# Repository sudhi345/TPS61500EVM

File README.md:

# TPS61500EVM
Evaluation board for TPS61500 high brightness led driver

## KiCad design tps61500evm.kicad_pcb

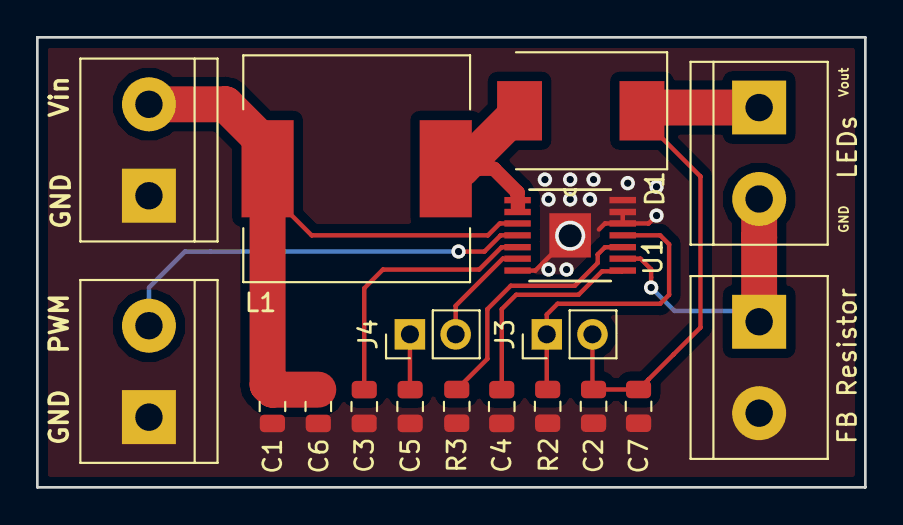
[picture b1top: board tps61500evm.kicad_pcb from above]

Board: 2 copper layers, 46.0 x 25.0 mm, 18 parts (0 on the bottom side), 12 nets.

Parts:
C1, C2: 10uF; C_0805_2012Metric
C3, C4: 0.1uF; C_0805_2012Metric
C5: 1uF; C_0805_2012Metric
C6, C7: C; C_0805_2012Metric
D1: SS54; D_SMC
J1: Vin; TerminalBlock_bornier-2_P5.08mm
J2: PWM; TerminalBlock_bornier-2_P5.08mm
J3: OVP_Resistor(R1); PinHeader_1x02_P2.54mm_Vertical
J4: EN_DIMC; PinHeader_1x02_P2.54mm_Vertical
J5: LEDs; TerminalBlock_bornier-2_P5.08mm
J6: FB Resistor; TerminalBlock_bornier-2_P5.08mm
L1: 15uH; L_12x12mm_H8mm
R2: 10k; R_0805_2012Metric
R3: 33k; R_0805_2012Metric
U1: TPS61500PWPR; SOP65P640X120-15N

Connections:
/DIMC: J4.2, U1.6
/FB: J5.2, J6.1, U1.9
/OVP: J3.1, R2.1, U1.11
/PWM: J2.2, U1.4
/SW: D1.2, L1.2, U1.1, U1.2
/Vin: C1.1, C6.1, J1.2, L1.1, U1.3
/Vout: C2.1, C7.1, D1.1, J3.2, J5.1
GND: C1.2, C2.2, C3.2, C4.2, C5.2, C6.2, C7.2, J1.1, J2.1, J6.2, R2.2, R3.2, U1.7, U1.12, U1.13, U1.14, U1.15
unnamed: C3.1, U1.5
unnamed: C4.1, U1.8
unnamed: C5.1, J4.1
unnamed: R3.1, U1.10

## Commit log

2019-07-07 Add files
2019-07-07 Updated files
2019-07-07 Create LICENSE
2019-07-12 New 3d view
2019-07-20 add datasheets
